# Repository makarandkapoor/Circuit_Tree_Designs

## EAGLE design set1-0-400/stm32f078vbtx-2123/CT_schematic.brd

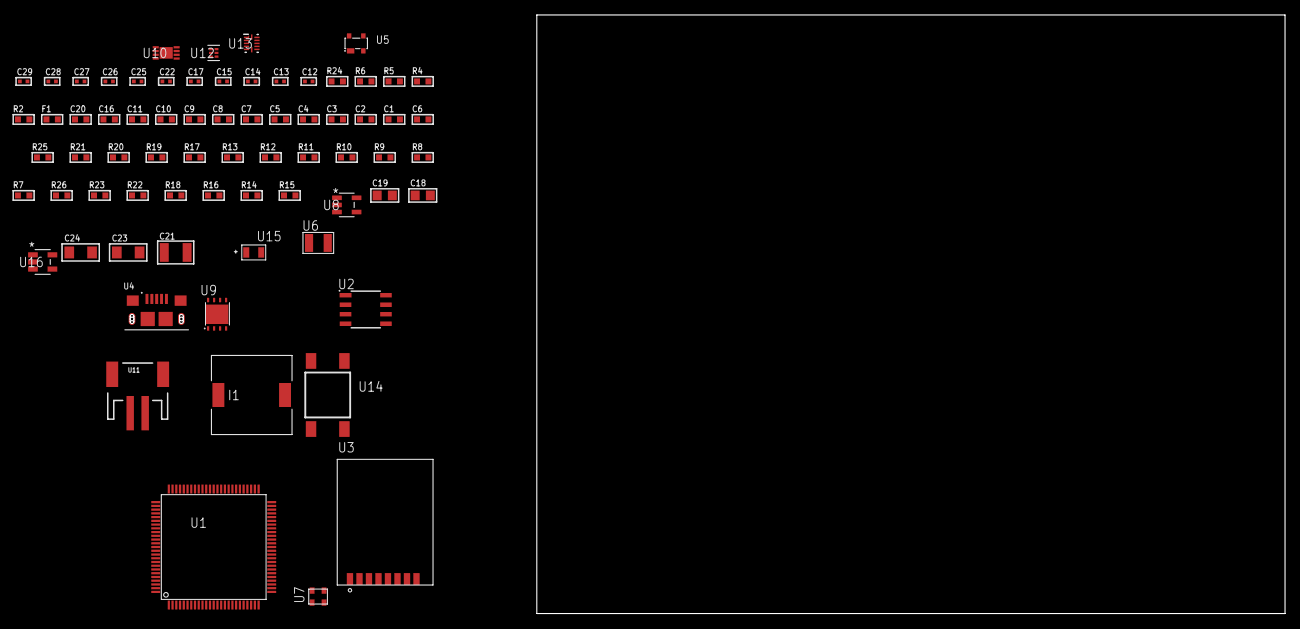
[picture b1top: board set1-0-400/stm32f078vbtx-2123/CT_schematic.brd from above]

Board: 2 copper layers, 71 parts (0 on the bottom side), 37 nets, no tracks yet.

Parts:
C1, C11, C16, C20: 1e-06; C0603
C2, C3, C4, C5, C7, C8, C9: 1e-07; C0603
C6: 4.7e-06; C0603
C10: 1e-08; C0603
C12, C13: 1e-11; C0402
C14, C17, C25, C27, C29: 1e-08; C0402
C15, C22, C26, C28: 1e-07; C0402
C18, C19: 1e-05; C0805
C21: 1e-05; C1210
C23, C24: 1e-05; C1206
F1: 240.0; L0603
I1: 5.2e-06; DR1040
R2: 1000.0; R0603
R4: 4700.0; R0603
R5, R6: 2200.0; R0603
R7, R8, R9, R10, R11, R12, R13, R19, R20, R25: 10000.0; R0603
R14: 490000.0; R0603
R15: 1000000.0; R0603
R16, R18: 100000.0; R0603
R17: 91000.0; R0603
R21: 82000.0; R0603
R22: 300000.0; R0603
R23: 120000.0; R0603
R24: 2000.0; R0603
R26: 200000.0; R0603
U1: stm32f078vbt6; LQFP100
U2: 24AA1025T-I/SN; SOIC-8
U3: RFM75-S
U4: 10118193-0001LF; FCI_10118193-0001LF
U5: prtr5v0u2ax; SOT143B
U6: ABS07-32.768KHZ-7-T
U7: ASDMB-25.000MHZ-EC-T; ASDMB-XX.XXXXMHZ-XX-XX-XXX
U8: ltc3406es5; TSOT-23-5
U9: LP2951ACSDX/NOPB; WSON-8
U10: MCP73831T-2ACI/MC; DFN8_2X3MC
U11: S2B-PH-SM4-TB(LF)(SN); JST-2-SMD
U12: TPS3895ADRYR; SON-6
U13: LSF0204DRUTR; RUT0012A
U14: 4-1437565-2; SW_4-1437565-2
U15: Q65110A2395; LGM67K-G1J2-24-Z
U16: nc7sz125m5x; NC7SZ125M5X

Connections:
CLK_CRYSTAL_U1_8: C12.1, U1.8, U6.1
CLK_CRYSTAL_U1_9: C13.1, U1.9, U6.2
CLK_U1_12: U1.12, U7.3
GND: C1.2, C2.2, C3.2, C4.2, C5.2, C6.2, C7.2, C8.2, C9.2, C10.2, C11.2, C12.2, C13.2, C14.2, C15.2, C16.2, C17.2, C18.2, C19.1, C19.2, C20.2, C21.2, C22.2, C23.2, C24.2, C25.2, C26.2, C27.2, C28.2, C29.2, R2.2, R7.2, R8.2, R11.2, R14.2, R18.2, R21.2, R23.2, R24.2, U1.20, U1.27, U1.49, U1.74, U1.99, U2.4, U3.1, U4.5, U4.6, U4.7, U4.8, U4.9, U5.1, U7.2, U8.2, U9.3, U9.4, U9.PAD, U10.6, U10.9, U11.2, U12.2, U13.6, U15.C, U16.1, U16.3
INPUT_USBPOWER_5V: C23.1, R25.2, U4.1, U5.4, U10.1, U10.2
NET_U1_14: R4.1, U1.14, U16.4
NET_U1_21: C10.1, C11.1, F1.1, U1.21
NET_U1_37: R8.1, U1.37
NET_U1_92: R5.1, U1.92, U2.6
NET_U1_93: R6.1, U1.93, U2.5
NET_U1_94: R7.1, U1.94
NET_U1_98: U14.3, U14.4
NET_U2_1: R10.1, U2.1
NET_U2_2: R11.1, U2.2
NET_U2_3: R9.1, U2.3
NET_U3_3: R12.1, U3.3
NET_U8_3: I1.1, U8.3
NET_U8_5: R14.1, R15.1, U8.5
NET_U8_ATNET_3: I1.2, R15.2
NET_U9_5: R16.1, U9.5
NET_U9_7: R17.2, R18.1, U9.7
NET_U10_5: R25.1, U10.5
NET_U10_8: R24.1, U10.8
NET_U12_1: R20.1, R21.1, U12.1
NET_U12_3: R22.2, R23.1, U12.3
NET_U12_4: R19.1, U12.4, U16.2
NET_U13_12: R26.1, U13.12
NET_U14_1: R2.1, U14.1, U14.2
PROC_SPI1_MISO_TOXCVR: U3.7, U13.9
PROC_SPI1_MOSI_TOXCVR: U3.6, U13.10
PROC_SPI1_NSS_TOXCVR: R13.1, U3.4, U13.7
PROC_SPI1_SCK_TOXCVR: U3.5, U13.8
PROC_USB_DM: U1.70, U4.2, U5.3
PROC_USB_DP: U1.71, U4.3, U5.2
VCC_S1_3V7: C18.1, C20.1, C24.1, U8.4, U9.8, U10.3, U10.4, U11.1
VCC_TIER1_1V8: C1.1, C2.1, C3.1, C4.1, C5.1, C6.1, C7.1, C8.1, C9.1, C14.1, C17.1, C19.2, C22.1, C27.1, C28.1, C29.1, F1.2, I1.2, R4.2, R5.2, R6.2, R9.2, R10.2, R15.2, R19.2, R20.2, R22.1, R26.2, U1.6, U1.28, U1.50, U1.75, U1.100, U2.7, U2.8, U7.4, U12.6, U13.1, U16.5
VCC_TIER1_2V5: C15.1, C16.1, C21.1, C25.1, C26.1, R12.2, R13.2, R16.2, R17.1, U3.2, U9.1, U13.11

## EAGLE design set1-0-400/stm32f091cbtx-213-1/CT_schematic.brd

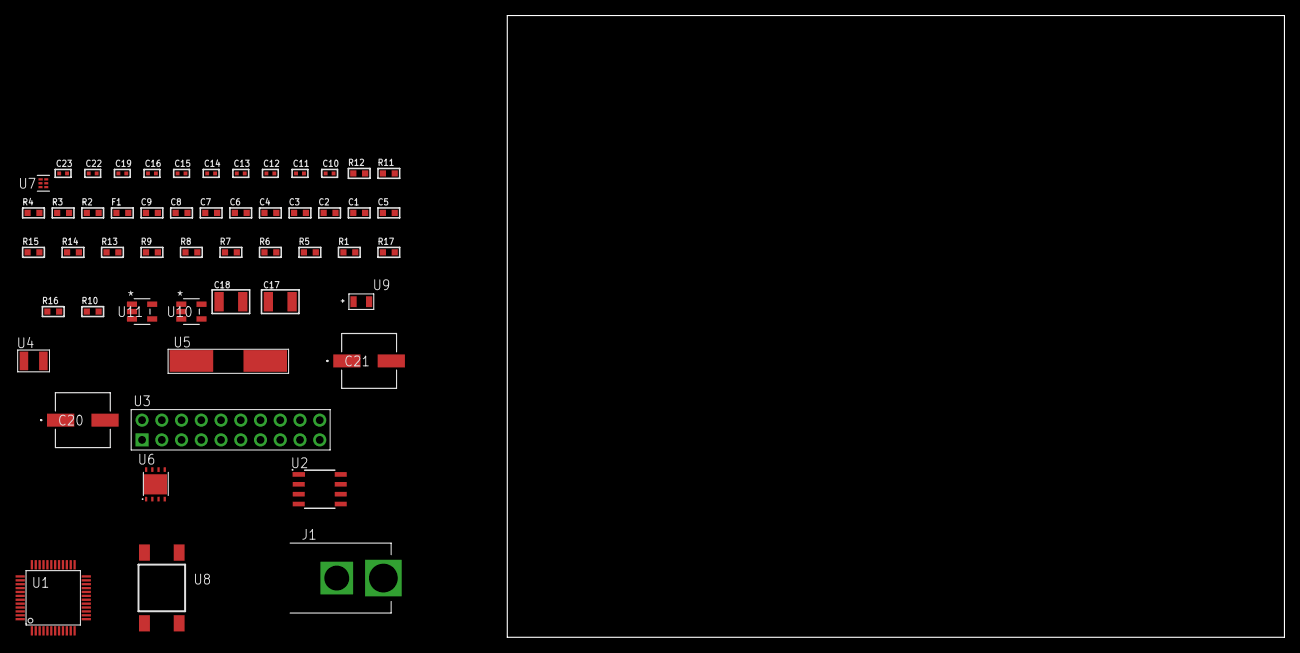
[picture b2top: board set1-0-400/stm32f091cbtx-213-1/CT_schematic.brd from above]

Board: 2 copper layers, 100.0 x 80.0 mm, 53 parts (0 on the bottom side), 28 nets, no tracks yet.

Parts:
C1, C9: 1e-06; C0603
C2, C3, C4, C6, C7: 1e-07; C0603
C5: 4.7e-06; C0603
C8: 1e-08; C0603
C10, C11, C12, C13: 1e-11; C0402
C14, C16, C22, C23: 1e-08; C0402
C15, C19: 1e-07; C0402
C17, C18: 1e-05; C1210
C20, C21: 0.0001; EXV-9H
F1: 240.0; L0603
J1: PJ-037B; PJ-037B_PACKAGE
R1, R5, R6, R7, R8, R9, R13, R14: 10000.0; R0603
R2, R12: 1000.0; R0603
R3: 1270.0; R0603
R4: 4700.0; R0603
R10: 100000.0; R0603
R11: 1500.0; R0603
R15: 18000.0; R0603
R16: 470000.0; R0603
R17: 120000.0; R0603
U1: stm32f091cbt6; LQFP48
U2: AT25320B-SSHL-T; SOIC-8
U3: TST-110-05-T-D-RA
U4: ABS07-32.768KHZ-7-T
U5: ABLS-25.000MHZ-B2F-T
U6: LP3878SDX-ADJ/NOPB; WSON-8
U7: TPS3895ADRYR; SON-6
U8: 4-1437565-2; SW_4-1437565-2
U9: Q65110A2395; LGM67K-G1J2-24-Z
U10, U11: nc7sz125m5x; NC7SZ125M5X

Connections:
CLK_CRYSTAL_U1_3: C10.1, U1.3, U4.1
CLK_CRYSTAL_U1_4: C11.1, U1.4, U4.2
CLK_CRYSTAL_U1_5: C12.1, U1.5, U5.1
CLK_CRYSTAL_U1_6: C13.1, U1.6, U5.2
GND: C1.2, C2.2, C3.2, C4.2, C5.2, C6.2, C7.2, C8.2, C9.2, C10.2, C11.2, C12.2, C13.2, C14.2, C15.2, C16.2, C17.2, C18.2, C19.2, C20.2, C21.2, C22.2, C23.2, J1.2, R2.2, R5.2, R12.2, R15.2, R17.2, U1.8, U1.23, U1.35, U1.47, U2.4, U3.4, U3.6, U3.8, U3.10, U3.12, U3.14, U3.16, U3.18, U3.20, U6.3, U6.PAD, U7.2, U9.C, U10.2, U10.3, U11.1, U11.3
NET_U1_7: R4.1, U1.7, U11.4
NET_U1_9: C8.1, C9.1, F1.1, U1.9
NET_U1_44: R5.1, U1.44
NET_U1_45: R3.1, U1.45, U9.A
NET_U1_46: R1.1, U1.46, U8.3, U8.4
NET_U2_3: R6.1, U2.3
NET_U2_7: R8.1, U2.7
NET_U6_1: C16.1, U6.1
NET_U6_6: R11.2, R12.1, U6.6
NET_U6_8: R10.1, U6.8
NET_U7_1: R14.1, R15.1, U7.1
NET_U7_3: R16.2, R17.1, U7.3
NET_U7_4: R13.1, U7.4, U10.4, U11.2
NET_U8_1: R2.1, U8.1, U8.2
PROC_SPI1_MISO: U1.16, U2.2
PROC_SPI1_MOSI: U1.17, U2.5
PROC_SPI1_NSS: R7.1, U1.14, U2.1
PROC_SPI1_SCK: U1.15, U2.6
PROC_SYS_SWCLK: U1.37, U3.9
PROC_SYS_SWDIO: U1.34, U3.7
RST_OUT_U3_SRESET_B: R9.1, U3.15, U10.1
VCC_S1_11V6: C17.1, C20.1, C21.1, J1.1, R10.2, U6.4
VCC_TIER1_2V5: C1.1, C2.1, C3.1, C4.1, C5.1, C6.1, C7.1, C14.1, C15.1, C18.1, C19.1, C22.1, C23.1, F1.2, R1.2, R3.2, R4.2, R6.2, R7.2, R8.2, R9.2, R11.1, R13.2, R14.2, R16.1, U1.1, U1.24, U1.36, U1.48, U2.8, U3.1, U6.5, U7.6, U10.5, U11.5

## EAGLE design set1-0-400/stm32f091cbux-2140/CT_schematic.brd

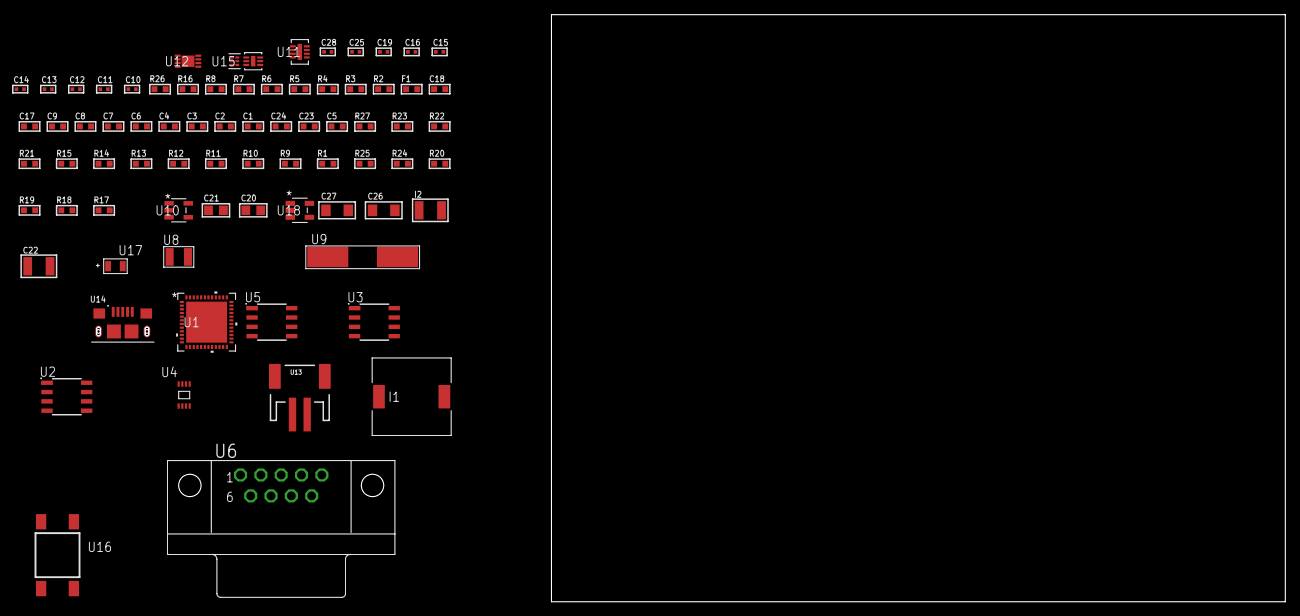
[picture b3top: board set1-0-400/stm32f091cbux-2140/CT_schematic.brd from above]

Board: 2 copper layers, 162.0 x 80.0 mm, 76 parts (0 on the bottom side), 48 nets, no tracks yet.

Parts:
C1, C9, C17, C18: 1e-06; C0603
C2, C3, C4, C6, C7: 1e-07; C0603
C5: 4.7e-06; C0603
C8: 1e-08; C0603
C10, C11, C12, C13: 1e-11; C0402
C14, C15, C16, C28: 1e-08; C0402
C19, C25: 1e-07; C0402
C20, C21: 1e-05; C0805
C22: 1e-05; C1210
C23: 2.2e-06; C0603
C24: 2.2e-07; C0603
C26, C27: 1e-05; C1206
F1: 240.0; L0603
I1: 3.8e-06; DR1040
I2: 1e-05; L1210
R1, R9, R10, R11, R12, R13, R14, R15, R21, R22, R27: 10000.0; R0603
R2: 1000.0; R0603
R3: 1270.0; R0603
R4: 4700.0; R0603
R5, R6, R7, R8: 2200.0; R0603
R16: 120.0; R0603
R17: 309473.68421053; R0603
R18: 1000000.0; R0603
R19: 100000.0; R0603
R20: 560000.0; R0603
R23: 18000.0; R0603
R24: 470000.0; R0603
R25: 120000.0; R0603
R26: 2000.0; R0603
U1: stm32f091cbu7; UFQFPN48
U2: AT25160B-SSHL-T; SOIC-8
U3: AT25256B-SSHL-T; SOIC-8
U4: 24AA08T-I/MNY; TDFN-8/6MM
U5: MCP2562-E/SN; SOIC-8
U6: 182-009-113R531; 182-009-MALE
U7: Si7051-A20-IM; DFN-6
U8: ABS07-32.768KHZ-7-T
U9: ABLS-25.000MHZ-B2F-T
U10: ltc3406es5; TSOT-23-5
U11: LT3494AEDDB#TRMPBF; DFN-8_DDB
U12: MCP73831T-2ACI/MC; DFN8_2X3MC
U13: S2B-PH-SM4-TB(LF)(SN); JST-2-SMD
U14: 10118193-0001LF; FCI_10118193-0001LF
U15: TPS3895ADRYR; SON-6
U16: 4-1437565-2; SW_4-1437565-2
U17: Q65110A2395; LGM67K-G1J2-24-Z
U18: nc7sz125m5x; NC7SZ125M5X

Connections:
CLK_CRYSTAL_U1_3: C10.1, U1.3, U8.1
CLK_CRYSTAL_U1_4: C11.1, U1.4, U8.2
CLK_CRYSTAL_U1_5: C12.1, U1.5, U9.1
CLK_CRYSTAL_U1_6: C13.1, U1.6, U9.2
GND: C1.2, C2.2, C3.2, C4.2, C5.2, C6.2, C7.2, C8.2, C9.2, C10.2, C11.2, C12.2, C13.2, C14.2, C15.2, C16.2, C17.2, C18.2, C19.2, C20.2, C21.1, C21.2, C22.2, C23.2, C24.2, C25.2, C26.2, C27.2, C28.2, R2.2, R9.2, R17.2, R23.2, R25.2, R26.2, U1.8, U1.23, U1.35, U1.47, U1.49, U2.4, U3.4, U4.4, U5.2, U5.8, U6.5, U7.2, U7.7, U10.2, U11.2, U11.9, U12.6, U12.9, U13.2, U14.5, U14.6, U14.7, U14.8, U14.9, U15.2, U17.C, U18.1, U18.3
INPUT_USBPOWER_5V: C26.1, R27.2, U12.1, U12.2, U14.1
NET_U1_7: R4.1, U1.7, U18.4
NET_U1_9: C8.1, C9.1, F1.1, U1.9
NET_U1_22: R8.1, U1.22, U4.5
NET_U1_26: R7.1, U1.26, U4.6
NET_U1_30: R5.1, U1.30, U7.6
NET_U1_31: R6.1, U1.31, U7.1
NET_U1_44: R9.1, U1.44
NET_U1_45: R3.1, U1.45, U17.A
NET_U1_46: R1.1, U1.46, U16.3, U16.4
NET_U2_3: R10.1, U2.3
NET_U2_7: R12.1, U2.7
NET_U3_3: R13.1, U3.3
NET_U3_7: R15.1, U3.7
NET_U5_6: R16.2, U5.6
NET_U6_2: R16.2, U5.6, U6.2
NET_U6_3: R16.1, U5.7, U6.3
NET_U10_3: I1.1, U10.3
NET_U10_5: R17.1, R18.1, U10.5
NET_U10_ATNET_3: I1.2, R18.2
NET_U11_1: I2.1, U11.1
NET_U11_5: R19.1, U11.5
NET_U11_6: R20.1, U11.6
NET_U11_8: C24.1, U11.8
NET_U12_5: R27.1, U12.5
NET_U12_8: R26.1, U12.8
NET_U15_1: R22.1, R23.1, U15.1
NET_U15_3: R24.2, R25.1, U15.3
NET_U15_4: R21.1, U15.4, U18.2
NET_U16_1: R2.1, U16.1, U16.2
PROC_CAN_RX: U1.32, U5.4
PROC_CAN_TX: U1.33, U5.1
PROC_SPI1_MISO: U1.16, U3.2
PROC_SPI1_MOSI: U1.17, U3.5
PROC_SPI1_NSS: R14.1, U1.14, U3.1
PROC_SPI1_SCK: U1.15, U3.6
PROC_SPI2_MISO: U1.27, U2.2
PROC_SPI2_MOSI: U1.28, U2.5
PROC_SPI2_NSS: R11.1, U1.25, U2.1
PROC_SPI2_SCK: U1.21, U2.6
VCC_S1_3V7: C20.1, C22.1, C27.1, I2.2, R19.2, U10.4, U11.3, U11.4, U12.3, U12.4, U13.1
VCC_TIER1_2V5: C1.1, C2.1, C3.1, C4.1, C5.1, C6.1, C7.1, C14.1, C15.1, C16.1, C18.1, C19.1, C21.2, C25.1, C28.1, F1.2, I1.2, R1.2, R3.2, R4.2, R5.2, R6.2, R7.2, R8.2, R10.2, R11.2, R12.2, R13.2, R14.2, R15.2, R18.2, R21.2, R22.2, R24.1, U1.1, U1.24, U1.36, U1.48, U2.8, U3.8, U4.7, U4.8, U5.5, U7.5, U15.6, U18.5
VCC_TIER1_5V0: C17.1, C23.1, R20.2, U5.3, U11.7

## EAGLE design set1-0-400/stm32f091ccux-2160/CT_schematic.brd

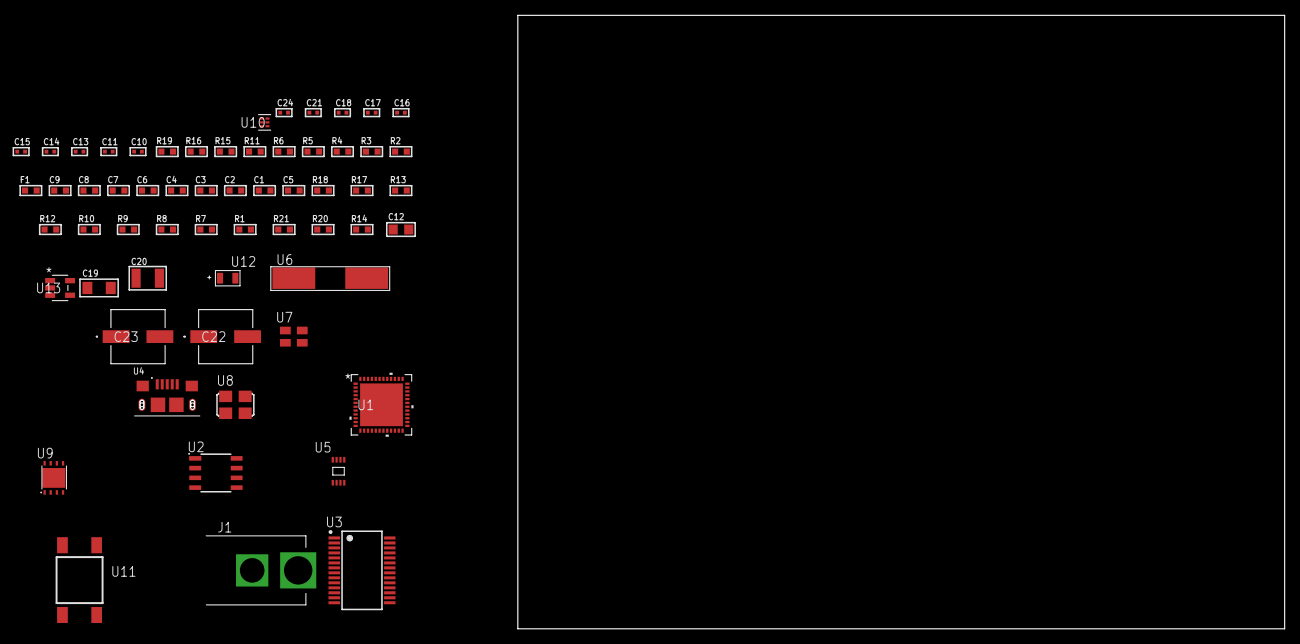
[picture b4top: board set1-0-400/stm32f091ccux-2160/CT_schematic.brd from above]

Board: 2 copper layers, 60 parts (0 on the bottom side), 37 nets, no tracks yet.

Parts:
C1, C9: 1e-06; C0603
C2, C3, C4, C6, C7: 1e-07; C0603
C5: 4.7e-06; C0603
C8: 1e-08; C0603
C10, C15, C16, C17, C18, C24: 1e-08; C0402
C11, C13, C14, C21: 1e-07; C0402
C12: 4.7e-06; C0805
C19: 1e-05; C1206
C20: 1e-05; C1210
C22, C23: 0.0001; EXV-9H
F1: 240.0; L0603
J1: PJ-037B; PJ-037B_PACKAGE
R1, R7, R8, R9, R10, R12, R13, R17, R18: 10000.0; R0603
R2, R16: 1000.0; R0603
R3: 1600.5; R0603
R4, R11: 4700.0; R0603
R5, R6: 2200.0; R0603
R14: 100000.0; R0603
R15: 2231.0; R0603
R19: 9100.0; R0603
R20: 680000.0; R0603
R21: 120000.0; R0603
U1: stm32f091ccu7; UFQFPN48
U2: AT25M02-SSHD-T; SOIC-8
U3: FT232RL-REEL; SSOP-28
U4: 10118193-0001LF; FCI_10118193-0001LF
U5: 24AA01T-I/MNY; TDFN-8/6MM
U6: ABLS-12.000MHZ-B4-T
U7: ASEK-32.768KHz-ECST; ASEK
U8: ASFL1-25MHZ-NCS; ASFL1
U9: LP3878SDX-ADJ/NOPB; WSON-8
U10: TPS3895ADRYR; SON-6
U11: 4-1437565-2; SW_4-1437565-2
U12: Q65110A2395; LGM67K-G1J2-24-Z
U13: nc7sz125m5x; NC7SZ125M5X

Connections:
CLK_CRYSTAL_U3_27: U3.27, U6.1
CLK_CRYSTAL_U3_28: U3.28, U6.2
CLK_U1_3: U1.3, U7.3
CLK_U1_5: U1.5, U8.3
GND: C1.2, C2.2, C3.2, C4.2, C5.2, C6.2, C7.2, C8.2, C9.2, C10.2, C11.2, C12.2, C13.2, C14.2, C15.2, C16.2, C17.2, C18.2, C19.2, C20.2, C21.2, C22.2, C23.2, C24.2, J1.2, R2.2, R7.2, R13.2, R16.2, R19.2, R21.2, U1.8, U1.23, U1.35, U1.47, U1.49, U2.4, U3.7, U3.18, U3.21, U3.25, U3.26, U4.5, U4.6, U4.7, U4.8, U4.9, U5.4, U5.7, U7.2, U8.2, U9.3, U9.PAD, U10.2, U12.C, U13.1, U13.3
NET_U1_6: R5.1, U1.6, U5.6
NET_U1_7: R4.1, U1.7, U13.4
NET_U1_9: C8.1, C9.1, F1.1, U1.9
NET_U1_43: R6.1, U1.43, U5.5
NET_U1_44: R7.1, U1.44
NET_U1_45: R3.1, U1.45, U12.A
NET_U1_46: R1.1, U1.46, U11.3, U11.4
NET_U2_3: R8.1, U2.3
NET_U2_7: R10.1, U2.7
NET_U3_14: R12.1, U3.14
NET_U3_17: C13.1, U3.17
NET_U3_19: R13.1, U3.19
NET_U4_1: R11.1, U4.1
NET_U4_2: U3.16, U4.2
NET_U4_3: U3.15, U4.3
NET_U9_1: C18.1, U9.1
NET_U9_6: R15.2, R16.1, U9.6
NET_U9_8: R14.1, U9.8
NET_U10_1: R18.1, R19.1, U10.1
NET_U10_3: R20.2, R21.1, U10.3
NET_U10_4: R17.1, U10.4, U13.2
NET_U11_1: R2.1, U11.1, U11.2
PROC_SPI1_MISO: U1.16, U2.2
PROC_SPI1_MOSI: U1.17, U2.5
PROC_SPI1_NSS: R9.1, U1.14, U2.1
PROC_SPI1_SCK: U1.15, U2.6
PROC_USART1_CTS: U1.32, U3.3
PROC_USART1_RTS: U1.33, U3.11
PROC_USART1_RX: U1.31, U3.1
PROC_USART1_TX: U1.30, U3.5
VCC_S1_5V9: C19.1, C22.1, C23.1, J1.1, R14.2, U9.4
VCC_TIER1_3V3: C1.1, C2.1, C3.1, C4.1, C5.1, C6.1, C7.1, C10.1, C11.1, C12.1, C14.1, C15.1, C16.1, C17.1, C20.1, C21.1, C24.1, F1.2, R1.2, R3.2, R4.2, R5.2, R6.2, R8.2, R9.2, R10.2, R12.2, R15.1, R17.2, R18.2, R20.1, U1.1, U1.24, U1.36, U1.48, U2.8, U3.4, U3.20, U5.8, U7.4, U8.4, U9.5, U10.6, U13.5

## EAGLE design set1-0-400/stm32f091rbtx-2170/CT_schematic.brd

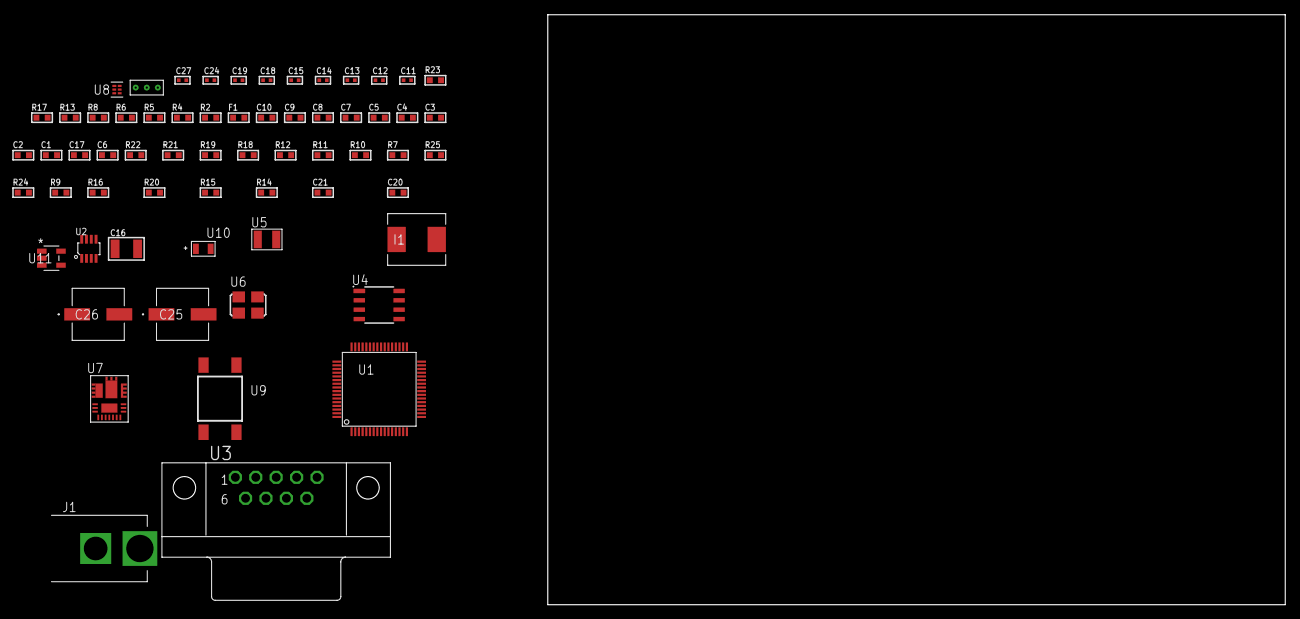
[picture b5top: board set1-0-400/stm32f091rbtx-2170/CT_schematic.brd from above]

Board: 2 copper layers, 100.0 x 80.0 mm, 63 parts (0 on the bottom side), 37 nets, no tracks yet.

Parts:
C1, C10: 1e-06; C0603
C2, C3, C4, C5, C7, C8: 1e-07; C0603
C6: 4.7e-06; C0603
C9: 1e-08; C0603
C11, C12: 1e-11; C0402
C13, C18, C19, C24: 1e-07; C0402
C14, C15, C27: 1e-08; C0402
C16: 0.0001; C1210
C17: 2.2e-06; C0603
C20: 8.7488758840791e-09; R0603
C21: 2.9825713241179e-07; R0603
C25, C26: 0.0001; EXV-9H
F1: 240.0; L0603
I1: 6.8e-07; IND25X25CZ
J1: PJ-037B; PJ-037B_PACKAGE
R2: 1000.0; R0603
R4: 4700.0; R0603
R5, R6: 2200.0; R0603
R7, R10, R11, R12, R21, R22: 10000.0; R0603
R8: 120.0; R0603
R9: 100000.0; R0603
R13: 0.1; R0603
R14: 4030.2416170974; R0603
R15: 719.68600305311; R0603
R16: 58.26650887574; R0603
R17: 130.0; R0603
R18: 39000.0; R0603
R19: 49900.0; R0603
R20: 5113.9346405229; R0603
R23: 9100.0; R0603
R24: 680000.0; R0603
R25: 120000.0; R0603
U1: stm32f091rbt6; LQFP64
U2: MAX3051EKA+T; SOT-23-8
U3: 182-009-113R531; 182-009-MALE
U4: 24AA1025T-I/SN; SOIC-8
U5: ABS07-32.768KHZ-7-T
U6: ASFL1-25MHZ-NCS; ASFL1
U7: IR3899MTR1PBF
U8: TPS3895ADRYR; SON-6
U9: 4-1437565-2; SW_4-1437565-2
U10: Q65110A2395; LGM67K-G1J2-24-Z
U11: nc7sz125m5x; NC7SZ125M5X
U12: Dummy; DUMMY_PACKAGE_127

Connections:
CLK_CRYSTAL_U1_3: C11.1, U1.3, U5.1
CLK_CRYSTAL_U1_4: C12.1, U1.4, U5.2
CLK_U1_5: U1.5, U6.3
GND: C1.2, C2.2, C3.2, C4.2, C5.2, C6.2, C7.2, C8.2, C9.2, C10.2, C11.2, C12.2, C13.2, C14.2, C15.2, C17.2, C18.2, C19.2, C24.2, C25.2, C26.2, C27.2, J1.2, R2.2, R7.2, R9.2, R11.2, R13.1, R13.2, R15.2, R18.2, R20.2, R23.2, R25.2, U1.12, U1.18, U1.31, U1.47, U1.63, U2.2, U3.5, U4.4, U4.7, U6.2, U7.4, U7.11, U7.17, U8.2, U10.C, U11.1, U11.3, U12.1
NET_U1_6: R5.1, U1.6, U4.6
NET_U1_7: R4.1, U1.7, U11.4
NET_U1_13: C9.1, C10.1, F1.1, U1.13
NET_U1_43: R6.1, U1.43, U4.5
NET_U1_60: R7.1, U1.60
NET_U1_62: U9.3, U9.4
NET_U2_6: R8.2, U2.6
NET_U2_8: R9.1, U2.8
NET_U3_2: R8.2, U2.6, U3.2
NET_U3_3: R8.1, U2.7, U3.3
NET_U4_1: R11.1, U4.1
NET_U4_2: R12.1, U4.2
NET_U4_3: R10.1, U4.3
NET_U7_1: C20.1, R14.1, R15.1, R16.1, R17.1, U7.1, U7.8
NET_U7_2: C19.1, U7.2
NET_U7_3: C20.2, C21.1, C21.2, U7.3
NET_U7_5: R18.1, U7.5
NET_U7_10: C17.1, U7.10
NET_U7_12: C16.1, I1.1, U7.12
NET_U7_14: C16.2, U7.14
NET_U7_15: R19.1, R20.1, U7.15
NET_U7_ATNET_3: I1.2, R14.2
NET_U7_ATNET_4: C21.2, R16.2
NET_U8_1: R22.1, R23.1, U8.1
NET_U8_3: R24.2, R25.1, U8.3
NET_U8_4: R21.1, U8.4, U11.2
NET_U9_1: R2.1, U9.1, U9.2
PROC_CAN_RX: U1.44, U2.4
PROC_CAN_TX: U1.45, U2.1
PROC_PC0: U1.8, U12.3
PROC_PC13: U1.2, U12.2
VCC_S1_16V9: C18.1, C25.1, C26.1, J1.1, R19.2, U7.9
VCC_TIER1_3V3: C1.1, C2.1, C3.1, C4.1, C5.1, C6.1, C7.1, C8.1, C13.1, C14.1, C15.1, C24.1, C27.1, F1.2, I1.2, R4.2, R5.2, R6.2, R10.2, R12.2, R14.2, R21.2, R22.2, R24.1, U1.1, U1.19, U1.32, U1.48, U1.64, U2.3, U4.8, U6.4, U8.6, U11.5

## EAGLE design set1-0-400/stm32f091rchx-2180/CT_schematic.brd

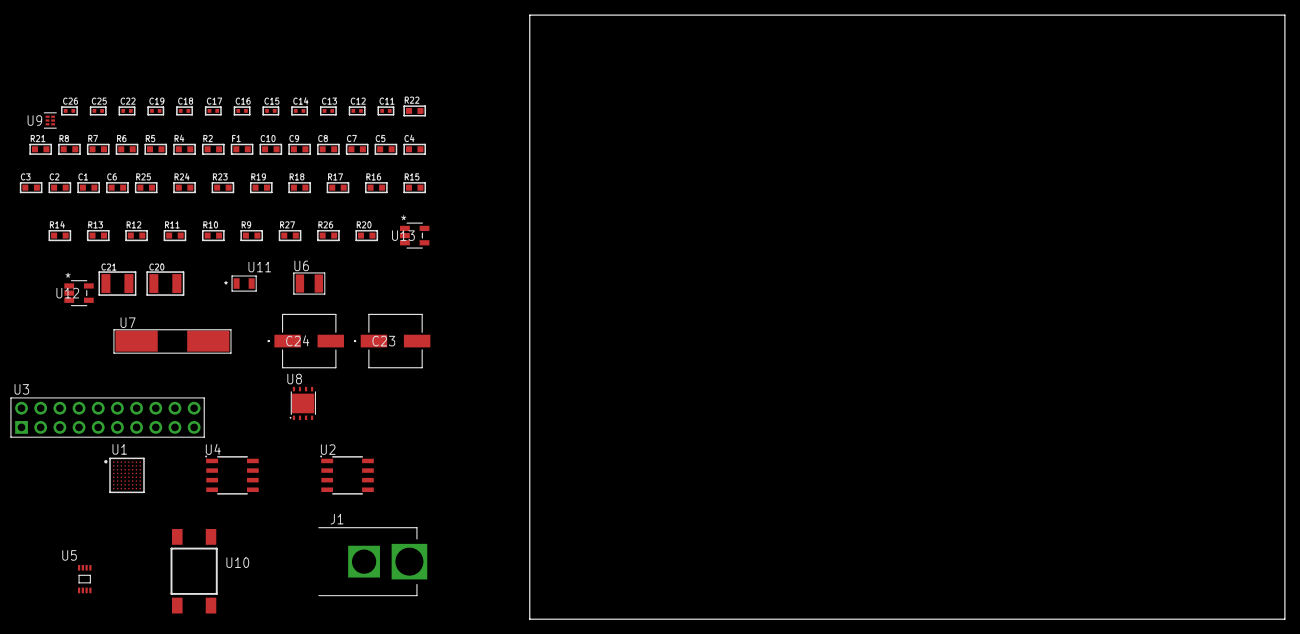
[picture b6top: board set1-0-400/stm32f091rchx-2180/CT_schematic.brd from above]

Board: 2 copper layers, 100.0 x 80.0 mm, 66 parts (0 on the bottom side), 35 nets, no tracks yet.

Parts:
C1, C10: 1e-06; C0603
C2, C3, C4, C5, C7, C8: 1e-07; C0603
C6: 4.7e-06; C0603
C9: 1e-08; C0603
C11, C12, C13, C14: 1e-11; C0402
C15, C17, C18, C19, C25, C26: 1e-08; C0402
C16, C22: 1e-07; C0402
C20, C21: 1e-05; C1210
C23, C24: 0.0001; EXV-9H
F1: 240.0; L0603
J1: PJ-037B; PJ-037B_PACKAGE
R2, R22: 1000.0; R0603
R4: 4700.0; R0603
R5, R6, R7, R8: 2200.0; R0603
R9, R10, R11, R12, R13, R14, R15, R16, R17, R18, R19, R23, R24: 10000.0; R0603
R20: 100000.0; R0603
R21: 1500.0; R0603
R25: 18000.0; R0603
R26: 470000.0; R0603
R27: 120000.0; R0603
U1: stm32f091rch7; UFBGA64
U2: AT25020B-SSHL-T; SOIC-8
U3: TST-110-05-T-D-RA
U4: 24AA1025T-I/SN; SOIC-8
U5: 24AA64T-I/MNY; TDFN-8/6MM
U6: ABS07-32.768KHZ-7-T
U7: ABLS-25.000MHZ-B2F-T
U8: LP3878SDX-ADJ/NOPB; WSON-8
U9: TPS3895ADRYR; SON-6
U10: 4-1437565-2; SW_4-1437565-2
U11: Q65110A2395; LGM67K-G1J2-24-Z
U12, U13: nc7sz125m5x; NC7SZ125M5X

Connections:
CLK_CRYSTAL_U1_A1: C11.1, U1.A1, U6.1
CLK_CRYSTAL_U1_B1: C12.1, U1.B1, U6.2
CLK_CRYSTAL_U1_C1: C13.1, U1.C1, U7.1
CLK_CRYSTAL_U1_D1: C14.1, U1.D1, U7.2
GND: C1.2, C2.2, C3.2, C4.2, C5.2, C6.2, C7.2, C8.2, C9.2, C10.2, C11.2, C12.2, C13.2, C14.2, C15.2, C16.2, C17.2, C18.2, C19.2, C20.2, C21.2, C22.2, C23.2, C24.2, C25.2, C26.2, J1.2, R2.2, R9.2, R15.2, R18.2, R19.2, R22.2, R25.2, R27.2, U1.C2, U1.D4, U1.D5, U1.D6, U1.F1, U2.4, U3.4, U3.6, U3.8, U3.10, U3.12, U3.14, U3.16, U3.18, U3.20, U4.4, U4.7, U5.4, U8.3, U8.PAD, U9.2, U11.C, U12.2, U12.3, U13.1, U13.3
NET_U1_A3: R6.1, U1.A3, U4.5
NET_U1_B3: R5.1, U1.B3, U4.6
NET_U1_B4: R9.1, U1.B4
NET_U1_B8: R8.1, U1.B8, U5.5
NET_U1_C8: R7.1, U1.C8, U5.6
NET_U1_E1: R4.1, U1.E1, U13.4
NET_U1_H1: C9.1, C10.1, F1.1, U1.H1
NET_U1_H8: U10.3, U10.4
NET_U2_3: R10.1, U2.3
NET_U2_7: R12.1, U2.7
NET_U4_1: R15.1, U4.1
NET_U4_2: R16.1, U4.2
NET_U4_3: R14.1, U4.3
NET_U5_1: R17.1, U5.1
NET_U5_2: R18.1, U5.2
NET_U5_3: R19.1, U5.3
NET_U8_1: C19.1, U8.1
NET_U8_6: R21.2, R22.1, U8.6
NET_U8_8: R20.1, U8.8
NET_U9_1: R24.1, R25.1, U9.1
NET_U9_3: R26.2, R27.1, U9.3
NET_U9_4: R23.1, U9.4, U12.4, U13.2
NET_U10_1: R2.1, U10.1, U10.2
PROC_SPI1_MISO: U1.A4, U2.2
PROC_SPI1_MOSI: U1.C4, U2.5
PROC_SPI1_NSS: R11.1, U1.A6, U2.1
PROC_SPI1_SCK: U1.A5, U2.6
RST_OUT_U3_SRESET_B: R13.1, U3.15, U12.1
VCC_S1_11V6: C20.1, C23.1, C24.1, J1.1, R20.2, U8.4
VCC_TIER1_2V5: C1.1, C2.1, C3.1, C4.1, C5.1, C6.1, C7.1, C8.1, C15.1, C16.1, C17.1, C18.1, C21.1, C22.1, C25.1, C26.1, F1.2, R4.2, R5.2, R6.2, R7.2, R8.2, R10.2, R11.2, R12.2, R13.2, R14.2, R16.2, R17.2, R21.1, R23.2, R24.2, R26.1, U1.B2, U1.D2, U1.E4, U1.E5, U1.E6, U2.8, U3.1, U4.8, U5.7, U5.8, U8.5, U9.6, U12.5, U13.5

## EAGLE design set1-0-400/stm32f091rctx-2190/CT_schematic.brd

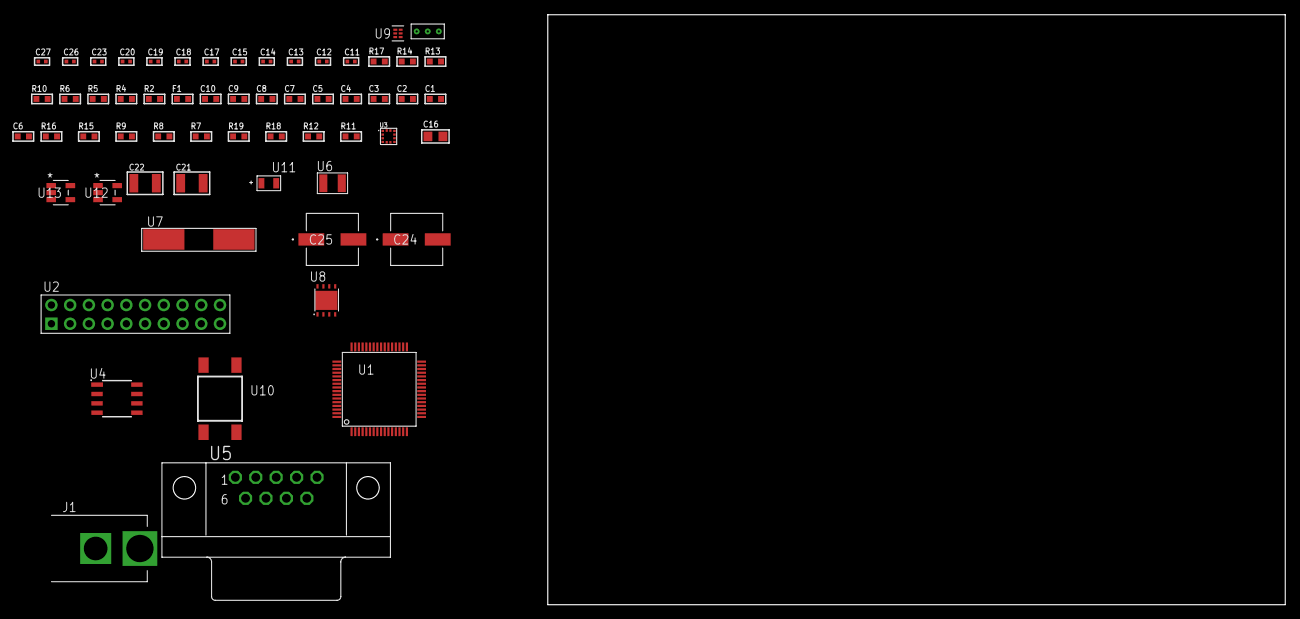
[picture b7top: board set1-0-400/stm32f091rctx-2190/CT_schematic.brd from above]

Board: 2 copper layers, 100.0 x 80.0 mm, 60 parts (0 on the bottom side), 32 nets, no tracks yet.

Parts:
C1, C10: 1e-06; C0603
C2, C3, C4, C5, C7, C8: 1e-07; C0603
C6: 4.7e-06; C0603
C9: 1e-08; C0603
C11, C12, C13, C14: 1e-11; C0402
C15, C17, C18, C19, C23: 1e-07; C0402
C16: 1e-05; C0805
C20, C26, C27: 1e-08; C0402
C21, C22: 1e-05; C1210
C24, C25: 0.0001; EXV-9H
F1: 240.0; L0603
J1: PJ-037B; PJ-037B_PACKAGE
R2, R14: 1000.0; R0603
R4: 4700.0; R0603
R5, R6: 2200.0; R0603
R7, R8, R9, R15, R16: 10000.0; R0603
R10: 120.0; R0603
R11, R12: 100000.0; R0603
R13: 2231.0; R0603
R17: 9100.0; R0603
R18: 680000.0; R0603
R19: 120000.0; R0603
U1: stm32f091rct6; LQFP64
U2: TST-110-05-T-D-RA
U3: LIS2HH12TR; LGA-12
U4: SN65HVD230D; SOIC-8
U5: 182-009-113R531; 182-009-MALE
U6: ABS07-32.768KHZ-7-T
U7: ABLS-25.000MHZ-B2F-T
U8: LP3878SDX-ADJ/NOPB; WSON-8
U9: TPS3895ADRYR; SON-6
U10: 4-1437565-2; SW_4-1437565-2
U11: Q65110A2395; LGM67K-G1J2-24-Z
U12, U13: nc7sz125m5x; NC7SZ125M5X
U14: Dummy; DUMMY_PACKAGE_129

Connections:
CLK_CRYSTAL_U1_3: C11.1, U1.3, U6.1
CLK_CRYSTAL_U1_4: C12.1, U1.4, U6.2
CLK_CRYSTAL_U1_5: C13.1, U1.5, U7.1
CLK_CRYSTAL_U1_6: C14.1, U1.6, U7.2
GND: C1.2, C2.2, C3.2, C4.2, C5.2, C6.2, C7.2, C8.2, C9.2, C10.2, C11.2, C12.2, C13.2, C14.2, C15.2, C16.2, C17.2, C18.2, C19.2, C20.2, C21.2, C22.2, C23.2, C24.2, C25.2, C26.2, C27.2, J1.2, R2.2, R7.2, R11.2, R14.2, R17.2, R19.2, U1.12, U1.18, U1.31, U1.47, U1.63, U2.4, U2.6, U2.8, U2.10, U2.12, U2.14, U2.16, U2.18, U2.20, U3.5, U3.6, U3.7, U3.8, U4.2, U5.5, U8.3, U8.PAD, U9.2, U11.C, U12.2, U12.3, U13.1, U13.3, U14.1
NET_U1_7: R4.1, U1.7, U13.4
NET_U1_13: C9.1, C10.1, F1.1, U1.13
NET_U1_42: R5.1, U1.42, U3.1
NET_U1_43: R6.1, U1.43, U3.4
NET_U1_60: R7.1, U1.60
NET_U1_62: U10.3, U10.4
NET_U3_2: R9.1, U3.2
NET_U4_6: R10.2, U4.6
NET_U4_8: R11.1, U4.8
NET_U5_2: R10.2, U4.6, U5.2
NET_U5_3: R10.1, U4.7, U5.3
NET_U8_1: C20.1, U8.1
NET_U8_6: R13.2, R14.1, U8.6
NET_U8_8: R12.1, U8.8
NET_U9_1: R16.1, R17.1, U9.1
NET_U9_3: R18.2, R19.1, U9.3
NET_U9_4: R15.1, U9.4, U12.4, U13.2
NET_U10_1: R2.1, U10.1, U10.2
PROC_CAN_RX: U1.44, U4.4
PROC_CAN_TX: U1.45, U4.1
PROC_PC0: U1.8, U14.3
PROC_PC13: U1.2, U14.2
PROC_SYS_SWCLK: U1.49, U2.9
PROC_SYS_SWDIO: U1.46, U2.7
RST_OUT_U2_SRESET_B: R8.1, U2.15, U12.1
VCC_S1_13V4: C21.1, C24.1, C25.1, J1.1, R12.2, U8.4
VCC_TIER1_3V3: C1.1, C2.1, C3.1, C4.1, C5.1, C6.1, C7.1, C8.1, C15.1, C16.1, C17.1, C18.1, C19.1, C22.1, C23.1, C26.1, C27.1, F1.2, R4.2, R5.2, R6.2, R8.2, R9.2, R13.1, R15.2, R16.2, R18.1, U1.1, U1.19, U1.32, U1.48, U1.64, U2.1, U3.9, U3.10, U4.3, U8.5, U9.6, U12.5, U13.5

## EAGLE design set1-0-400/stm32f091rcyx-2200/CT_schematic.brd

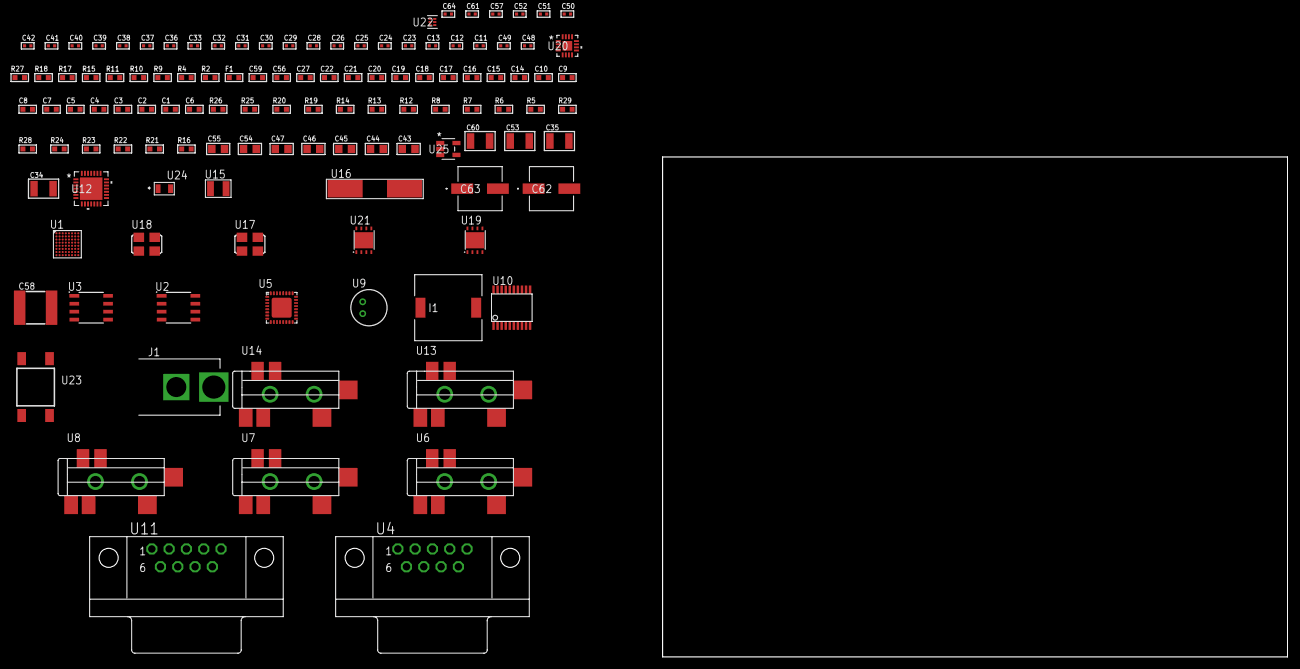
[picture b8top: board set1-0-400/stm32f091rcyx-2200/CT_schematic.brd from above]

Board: 2 copper layers, 100.0 x 80.0 mm, 119 parts (0 on the bottom side), 78 nets, no tracks yet.

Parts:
C1, C10, C14, C15, C16, C17, C18, C19, C20, C21, C22, C27, C56: 1e-06; C0603
C2, C3, C4, C5, C7, C8: 1e-07; C0603
C6: 4.7e-06; C0603
C9: 1e-08; C0603
C11, C12: 1e-11; C0402
C13, C50, C51, C52, C64: 1e-08; C0402
C23, C24, C25, C26, C28, C29, C30, C31, C32, C33, C38, C39, C40, C41, C42, C57, C61: 1e-07; C0402
C34, C35: 2.2e-05; C1210
C36, C37: 1e-09; C0402
C43, C44, C45, C46, C47, C54, C55: 1e-05; C0805
C48, C49: 2.2e-11; C0402
C53, C60: 1e-05; C1210
C58: 6.8e-05; 2220
C59: 8e-07; R0603
C62, C63: 0.0001; EXV-9H
F1: 240.0; L0603
I1: 7e-06; DR1040
J1: PJ-037B; PJ-037B_PACKAGE
R2, R18: 1000.0; R0603
R4: 4700.0; R0603
R5, R6, R7, R8, R25, R26: 10000.0; R0603
R9: 120.0; R0603
R10, R11: 1270.0; R0603
R12, R13, R14: 47000.0; R0603
R15: 680.0; R0603
R16, R22, R24: 100000.0; R0603
R17: 200.0; R0603
R19: 20000.0; R0603
R20: 91000.0; R0603
R21, R23: 300000.0; R0603
R27: 9100.0; R0603
R28: 680000.0; R0603
R29: 120000.0; R0603
U1: stm32f091rcy6; WLCSP64
U2: AT25040B-SSHL-T; SOIC-8
U3: MCP2562-E/SN; SOIC-8
U4, U11: 182-009-113R531; 182-009-MALE
U5: SGTL5000XNAA3; QFN-32
U6, U7, U8, U13, U14: SJ-43515TS-SMT-TR
U9: WM-64PCT; WM-64PC
U10: SP3203ECY-L/TR; TSSOP20-I
U12: WM8731CLSEFL; QFN-28
U15: ABS07-32.768KHZ-7-T
U16: ABLS-12.288MHZ-B4-T
U17: ASFL-24.57MHZ-NCS; ASFL1
U18: ASFL1-25MHZ-NCS; ASFL1
U19: LP3878SDX-ADJ/NOPB; WSON-8
U20: LTC3601EUD#PBF; QFN-16_EP
U21: LP2951ACSDX/NOPB; WSON-8
U22: TPS3895ADRYR; SON-6
U23: 4-1437565-2; SW_4-1437565-2
U24: Q65110A2395; LGM67K-G1J2-24-Z
U25: nc7sz125m5x; NC7SZ125M5X

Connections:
CLK_CRYSTAL_U1_C7: C11.1, U1.C7, U15.1
CLK_CRYSTAL_U1_C8: C12.1, U1.C8, U15.2
CLK_CRYSTAL_U12_1: C48.1, U12.1, U16.1
CLK_CRYSTAL_U12_2: C49.1, U12.2, U16.2
CLK_U1_D8: U1.D8, U18.3
CLK_U5_21: U5.21, U17.3
GND: C1.2, C2.2, C3.2, C4.2, C5.2, C6.2, C7.2, C8.2, C9.2, C10.2, C11.2, C12.2, C13.2, C14.2, C15.2, C23.2, C24.2, C25.2, C26.2, C27.2, C28.2, C29.2, C32.2, C33.2, C37.2, C38.2, C39.2, C40.2, C41.2, C42.2, C43.2, C44.2, C45.2, C46.2, C47.2, C48.2, C49.2, C50.2, C51.2, C52.2, C53.2, C54.2, C55.2, C56.2, C58.1, C58.2, C59.2, C60.2, C61.2, C62.2, C63.2, C64.2, J1.2, R2.2, R5.2, R11.2, R12.2, R13.2, R14.2, R18.2, R19.2, R21.2, R24.2, R27.2, R29.2, U1.A7, U1.B2, U1.G7, U1.G8, U1.H2, U2.4, U3.2, U3.8, U4.5, U5.1, U5.3, U5.7, U5.EXP, U7.1, U8.1, U9.2, U10.18, U11.5, U12.4, U12.15, U12.19, U12.25, U12.26, U12.29, U13.1, U14.1, U17.2, U18.2, U19.3, U19.PAD, U20.1, U20.9, U20.17, U21.3, U21.4, U21.PAD, U22.2, U24.C, U25.1, U25.3
NET_U1_C6: R5.1, U1.C6
NET_U1_D7: R4.1, U1.D7, U25.4
NET_U1_H7: U23.3, U23.4
NET_U1_H8: C9.1, C10.1, F1.1, U1.H8
NET_U2_3: R6.1, U2.3
NET_U2_7: R8.1, U2.7
NET_U3_6: R9.2, U3.6
NET_U4_2: R9.2, U3.6, U4.2
NET_U4_3: R9.1, U3.7, U4.3
NET_U5_10: C26.1, U5.10
NET_U5_29: R10.1, U5.29
NET_U5_31: R11.1, U5.31
NET_U6_1: U5.4, U6.1
NET_U6_2: U5.2, U6.2
NET_U6_5: U5.6, U6.5
NET_U7_2: C17.1, U7.2
NET_U7_5: C16.1, U7.5
NET_U8_2: C19.1, C20.1, U8.2
NET_U8_5: C18.1, U8.5
NET_U8_13: C19.2, C20.2
NET_U9_1: C21.1, C22.1, C27.1, U5.16, U9.1
NET_U9_15: C21.2, C22.2
NET_U10_1: C30.1, U10.1
NET_U10_2: C32.1, U10.2
NET_U10_3: C30.2, U10.3
NET_U10_4: C31.1, U10.4
NET_U10_5: C31.2, U10.5
NET_U10_6: C33.1, U10.6
NET_U11_2: U10.14, U11.2
NET_U11_3: U10.17, U11.3
NET_U11_7: U10.13, U11.7
NET_U11_8: U10.16, U11.8
NET_U12_20: C42.1, C47.1, U12.20
NET_U13_2: C35.1, R13.1, U13.2
NET_U13_5: C34.1, R12.1, U13.5
NET_U14_5: C36.1, C37.1, R14.1, R15.1, U14.5
NET_U19_1: C52.1, U19.1
NET_U19_6: R17.2, R18.1, U19.6
NET_U19_8: R16.1, U19.8
NET_U20_3: C57.2, I1.1, U20.3, U20.4
NET_U20_6: C57.1, U20.6
NET_U20_7: C56.1, U20.7, U20.12
NET_U20_10: R21.1, U20.10
NET_U20_11: R19.1, R20.1, U20.11
NET_U20_ATNET_3: I1.2, R20.2
NET_U21_5: R22.1, U21.5
NET_U21_7: R23.2, R24.1, U21.7
NET_U22_1: R26.1, R27.1, U22.1
NET_U22_3: R28.2, R29.1, U22.3
NET_U22_4: R25.1, U22.4, U25.2
NET_U23_1: R2.1, U23.1, U23.2
PROC_CAN_RX: U1.A6, U3.4
PROC_CAN_TX: U1.B6, U3.1
PROC_I2S1_CK: U1.F5, U12.7
PROC_I2S1_SD: U1.E4, U12.8
PROC_I2S1_WS: U1.H6, U12.9, U12.11
PROC_I2S2_CK: U1.F2, U5.24
PROC_I2S2_SD: U1.E6, U5.26
PROC_I2S2_WS: U1.G2, U5.23
PROC_SPI1_MISO: U1.D5, U2.2
PROC_SPI1_MOSI: U1.C5, U2.5
PROC_SPI1_NSS: R7.1, U1.A2, U2.1
PROC_SPI1_SCK: U1.D4, U2.6
PROC_USART1_CTS: U1.D3, U10.8
PROC_USART1_RTS: U1.B1, U10.10
PROC_USART1_RX: U1.B5, U10.11
PROC_USART1_TX: U1.A5, U10.7
VCC_S1_11V5: C53.1, C55.1, C59.1, C62.1, C63.1, J1.1, R16.2, U19.4, U20.15, U20.16, U21.8
VCC_TIER1_1V2: C23.1, C54.1, R17.1, U5.30, U19.5
VCC_TIER1_3V3: C1.1, C2.1, C3.1, C4.1, C5.1, C6.1, C7.1, C8.1, C13.1, C15.1, C24.1, C25.1, C28.1, C29.1, C38.1, C39.1, C40.1, C41.1, C43.1, C44.1, C45.1, C46.1, C50.1, C51.1, C58.2, C61.1, C64.1, F1.2, I1.2, R4.2, R6.2, R7.2, R8.2, R10.2, R20.2, R25.2, R26.2, R28.1, U1.A1, U1.A8, U1.B8, U1.G6, U1.H1, U2.8, U3.5, U5.5, U5.20, U10.12, U10.19, U12.3, U12.5, U12.12, U12.18, U17.4, U18.4, U20.8, U22.6, U25.5
VCC_TIER1_5V0: C14.1, C60.1, R22.2, R23.1, U3.3, U21.1

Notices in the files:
parts and their libraries:
circuit_tree: (C) 2014 Tomasz Boleslaw CEDRO, cederom@tlen.pl, http://www.tomek.cedro.info.
